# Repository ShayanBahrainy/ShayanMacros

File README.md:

# Shayan's Macros
A hackpad to open my most frequented websites/applications.
Reciever.py needs to run on your system and detects the keypresses from the keyboard and it can complete tasks for you.
For me it opens:

- Gmail
- YouTube "My Mix" playlist
- Visual Studio Code
- Terminal

But, it'll take like two seconds to change it to any other website or app.

# Inspiration
I wanted fun buttons, but buttons that did things so I might actually use them.

## Challenges

I didn't have access to Fusion360, like the original tutorial, so it took me longer than it should've to figure out how to import the DXF with the keyholes into my design. Luckily, someone in the Slack helped me.

## BOM:

Same as the original but with 4 leds.

-    4x Cherry MX Switches
-    4x SK6812 MINI Leds
-    1x XIAO RP2040
-    4x Blank DSA Keycaps
-    4x M3x16 Bolt
-    4x M3 Heatset
-    1x Alps EC11E Vertical H20mm Rotary Encoder

# Images

### PCB

### CAD

### Schematic

### Firmware

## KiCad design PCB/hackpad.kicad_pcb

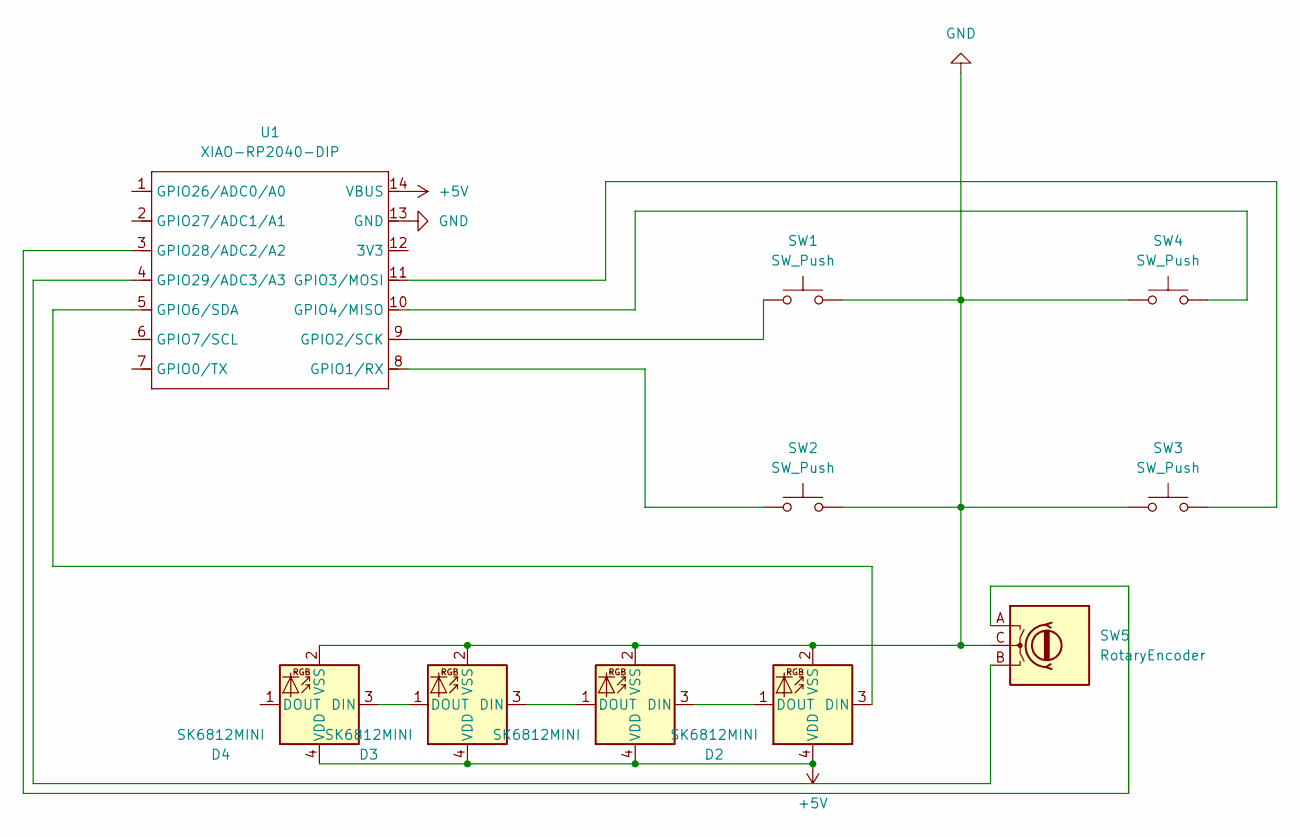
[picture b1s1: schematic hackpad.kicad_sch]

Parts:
D1, D2, D3, D4: SK6812MINI; LED_SK6812MINI_PLCC4_3.5x3.5mm_P1.75mm
SW1, SW2, SW3, SW4: SW_Push; SW_Cherry_MX_1.00u_PCB
SW5: RotaryEncoder; RotaryEncoder_Alps_EC11E_Vertical_H20mm
U1: XIAO-RP2040-DIP

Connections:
+5V: D1.4 (VDD), D2.4 (VDD), D3.4 (VDD), D4.4 (VDD), U1.14 (VBUS)
GND: D1.2 (VSS), D2.2 (VSS), D3.2 (VSS), D4.2 (VSS), SW1.2, SW2.2, SW3.1, SW4.1, SW5.C, U1.13 (GND)
unnamed: D1.3 (DIN), D2.1 (DOUT)
unnamed: D1.1 (DOUT), D3.3 (DIN)
unnamed: D2.3 (DIN), U1.5 (GPIO6/SDA)
unnamed: D3.1 (DOUT), D4.3 (DIN)
unnamed: SW2.1, U1.8 (GPIO1/RX)
unnamed: SW1.1, U1.9 (GPIO2/SCK)
unnamed: SW3.2, U1.11 (GPIO3/MOSI)
unnamed: SW4.2, U1.10 (GPIO4/MISO)
unnamed: SW5.A, U1.3 (GPIO28/ADC2/A2)
unnamed: SW5.B, U1.4 (GPIO29/ADC3/A3)

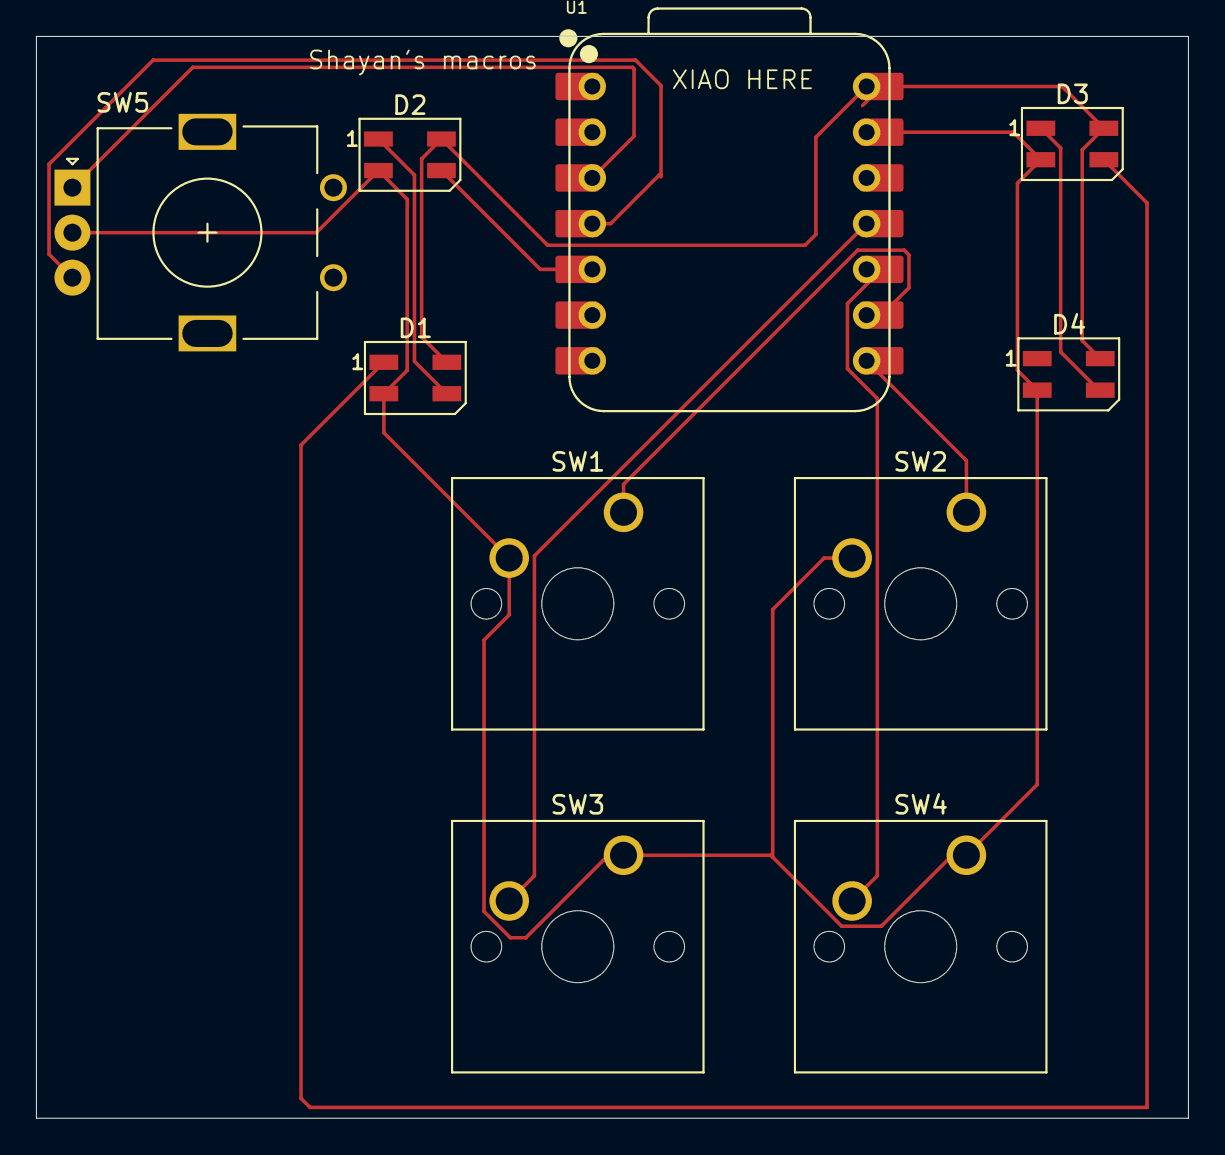
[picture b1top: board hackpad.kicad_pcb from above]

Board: 2 copper layers, 64.0 x 60.1 mm, 10 parts (0 on the bottom side), 12 nets.

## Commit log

2025-07-09 update project
2025-07-10 Added rotary-encoder
2025-07-10 Added hole for rotary encoder
